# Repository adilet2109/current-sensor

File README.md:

# current-sensor
Bare-metal code base for current sensor board

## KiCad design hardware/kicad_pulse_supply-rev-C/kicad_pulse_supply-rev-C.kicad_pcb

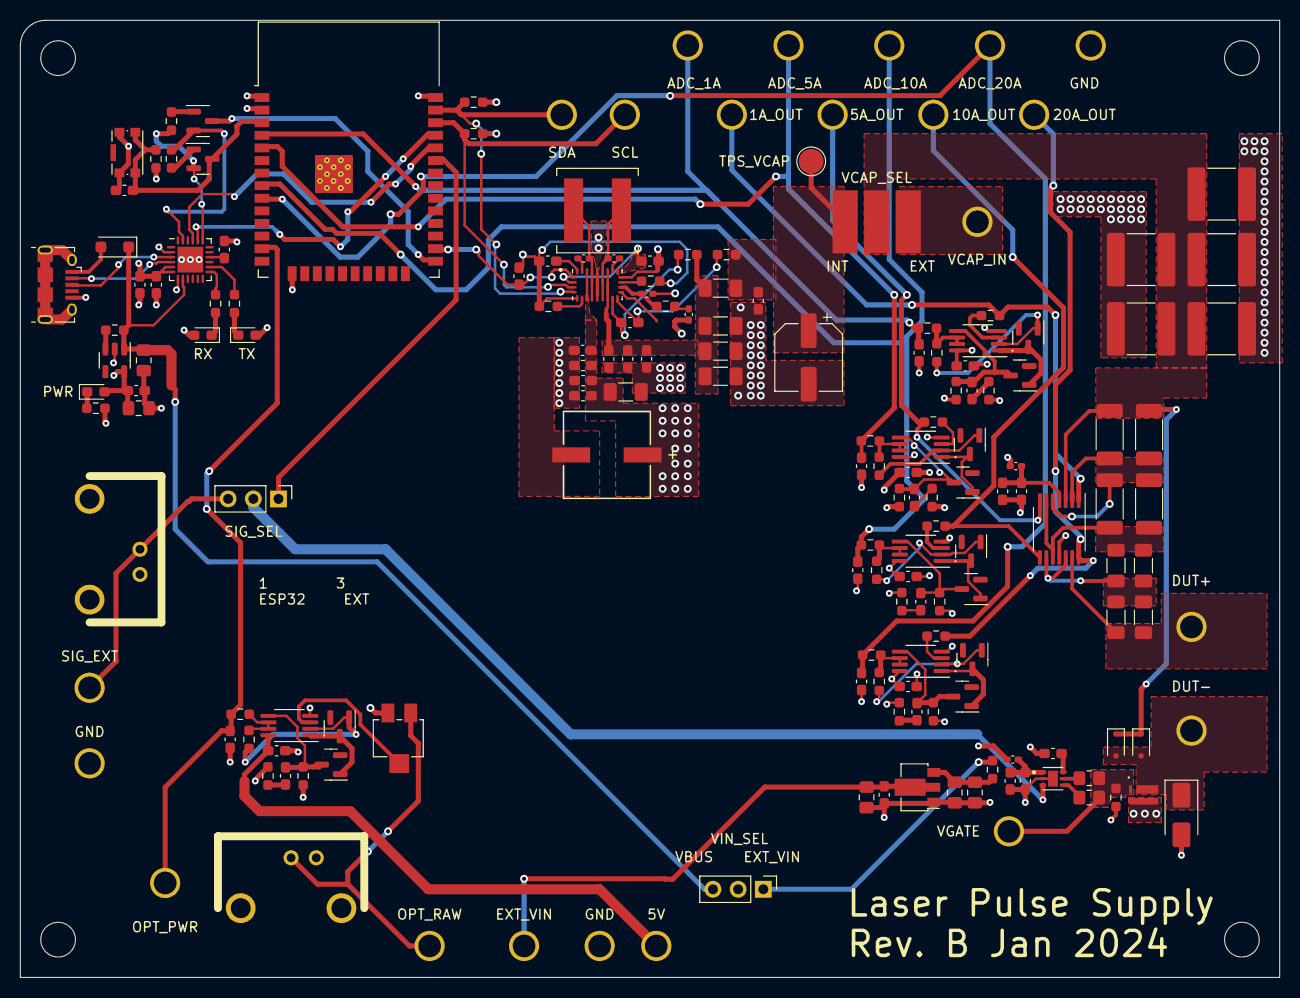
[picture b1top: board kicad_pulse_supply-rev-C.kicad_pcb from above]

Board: 4 copper layers, 127.0 x 96.5 mm, 179 parts (0 on the bottom side), 97 nets.

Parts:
C1, C3: 10u; C_0805_2012Metric_Pad1.18x1.45mm_HandSolder
C2, C4, C6, C7, C17, C18, C39, C40, C41, C42, C43, C51, C52, C59: 0u1; C_0603_1608Metric_Pad1.08x0.95mm_HandSolder
C5, C15, C16, C20, C53, C57: 1u; C_0603_1608Metric_Pad1.08x0.95mm_HandSolder
C8, C9, C10, C11, C12: 47u; C_2220_5650Metric
C14, C23, C24, C29, C32, C35: 100n; C_0603_1608Metric_Pad1.08x0.95mm_HandSolder
C19, C21, C22: 4u7; C_0805_2012Metric_Pad1.18x1.45mm_HandSolder
C25, C26, C30, C33, C36: 1u5; C_0603_1608Metric_Pad1.08x0.95mm_HandSolder
C27, C28, C31, C34, C37: 10n; C_0603_1608Metric_Pad1.08x0.95mm_HandSolder
C38: 4u7; C_0603_1608Metric_Pad1.08x0.95mm_HandSolder
C44, C54, C55, C56: 10u; C_1206_3216Metric_Pad1.33x1.80mm_HandSolder
C45: 68u; PCAP_EEHZ_F_PAN
C46, C49: 0u1; C_0402_1005Metric_Pad0.74x0.62mm_HandSolder
C47: 100p; C_0402_1005Metric_Pad0.74x0.62mm_HandSolder
C48: 4700p; C_0402_1005Metric_Pad0.74x0.62mm_HandSolder
C50: 0u22; C_0603_1608Metric_Pad1.08x0.95mm_HandSolder
C58: 100u; CP_Elec_6.3x5.8
D1: PWR; LED_0603_1608Metric_Pad1.05x0.95mm_HandSolder
D2: MBR120; D_SOD-123F
D3: TX; LED_0603_1608Metric_Pad1.05x0.95mm_HandSolder
D4: RX; LED_0603_1608Metric_Pad1.05x0.95mm_HandSolder
D5, D6: 100V 200mA; D_SOD-323F
D7: 24V 1W; D_SMA
D8, D9, D10, D11, D12, D13, D14, D15, D16, D17: BAT17; SOT-23
FB1, FB2: 330R 700mA; C_0402_1005Metric_Pad0.74x0.62mm_HandSolder
H1, H2, H3, H4: MountingHole; MountingHole_3.5mm
J1: USB_B_Micro; USB_Micro-B_Amphenol_10118194_Horizontal
J2: SIG_EXT; BNC_Molex_0731375003
J3: OPT_PWR; BNC_Molex_0731375003
JP1: SIG_SEL; PinHeader_1x03_P2.54mm_Vertical
JP2: VIN_SEL; PinHeader_1x03_P2.54mm_Vertical
JP3: VCAP_SEL; custom_jumper
L1: 4u7; L_Coilcraft_XAL7070-XXX
Q1, Q2: MMBT2222*; SOT-23
Q3: GAN7R0-150LBE; 3-FCLGA_3.2x2.2mm
R1, R2, R5, R14, R24, R25, R32, R37, R42: 10k; R_0603_1608Metric_Pad0.98x0.95mm_HandSolder
R3: 100k; R_0603_1608Metric_Pad0.98x0.95mm_HandSolder
R4, R8, R9, R26, R33, R38, R43: 1k; R_0603_1608Metric_Pad0.98x0.95mm_HandSolder
R6, R7, R22, R23, R31, R36, R41: 2k2; R_0603_1608Metric_Pad0.98x0.95mm_HandSolder
R10, R11: 0R3; R_2010_5025Metric_Pad1.40x2.65mm_HandSolder
R12, R13: 10; R_0805_2012Metric_Pad1.20x1.40mm_HandSolder
R15, R16: 0R06; R_2010_5025Metric_Pad1.40x2.65mm_HandSolder
R17, R18: 0R03; R_1206_3216Metric_Pad1.30x1.75mm_HandSolder
R19, R20: 0R015; R_1206_3216Metric_Pad1.30x1.75mm_HandSolder
R21: 0; R_0603_1608Metric_Pad0.98x0.95mm_HandSolder
R27, R28, R34, R39, R44: 1M; R_0603_1608Metric_Pad0.98x0.95mm_HandSolder
R29, R30, R35, R40, R45: 22; R_0603_1608Metric_Pad0.98x0.95mm_HandSolder
R47: 27k4; R_0603_1608Metric_Pad0.98x0.95mm_HandSolder
R48: 49k9; R_0603_1608Metric_Pad0.98x0.95mm_HandSolder
R49: 150k; R_0603_1608Metric_Pad0.98x0.95mm_HandSolder
R50, R51: 10; R_0603_1608Metric_Pad0.98x0.95mm_HandSolder
R52: 10m; R_1206_3216Metric_Pad1.30x1.75mm_HandSolder
RV1: 2k; Potentiometer_Bourns_3214X_Vertical
SW1: KMR211GLFS; SW_Push_1P1T-SH_NO_CK_KMR2xxG
TP1: SCL; Keystone-1502-2
TP2: SDA; Keystone-1502-2
TP3: VCAP_IN; Keystone-1502-2
TP4, TP10, TP16: GND; Keystone-1502-2
TP5: DUT+; Keystone-1502-2
TP6: VGATE; Keystone-1502-2
TP7: DUT-; Keystone-1502-2
TP8: 1A_OUT; Keystone-1502-2
TP9: SIG_EXT; Keystone-1502-2
TP11: 5A_OUT; Keystone-1502-2
TP12: 10A_OUT; Keystone-1502-2
TP13: 20A_OUT; Keystone-1502-2
TP14: 5V; Keystone-1502-2
TP15: EXT_VIN; Keystone-1502-2
TP17: ADC_1A; Keystone-1502-2
TP18: OPT_PEAK; Keystone-1502-2
TP19: ADC_5A; Keystone-1502-2
TP20: ADC_10A; Keystone-1502-2
TP21: ADC_20A; Keystone-1502-2
TP22: OPT_RAW; Keystone-1502-2
TP23: TPS_VCAP; TestPoint_Pad_D2.5mm
U1: AP2112K-3.3; SOT-23-5
U2: ESP32-WROOM-32D
U3: CP2104; QFN-24-1EP_4x4mm_P0.5mm_EP2.6x2.6mm
U4: MAX4378; TSSOP-14_4.4x5mm_P0.65mm
U5: UCC27611DRVT
U6: MCP1703T-5002E/MB; SOT-89-3
U7, U8, U9, U10, U11: LTC6244CMS8; MSOP-8_3x3mm_P0.65mm
U12: TPS552892RYQR; CONV_TPS552892RYQR

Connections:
+3V3: C2.1, C3.1, C5.1, C6.1, D1.2 (A), D3.2 (A), D4.2 (A), FB1.1, R2.2, R6.2, R7.2, U1.5 (VOUT), U2.2 (VDD), U3.5 (VIO), U3.6 (VDD), U3.7 (REGIN)
+5V: C23.1, C24.1, C29.1, C32.1, C35.1, C40.1, C41.1, C42.1, C43.1, C44.1, C45.1, FB2.1, JP2.2 (C), TP14.1, U7.8 (V+), U8.8 (V+), U9.8 (V+), U10.8 (V+), U11.8 (V+), U12.7 (VIN)
/Buck Boost Supply/BOOT1: C46.2, U12.20 (BOOT1)
/Buck Boost Supply/BOOT2: C49.2, U12.19 (BOOT2)
/Buck Boost Supply/COMP: C47.1, R47.1, U12.15 (COMP)
/Buck Boost Supply/ISN: C50.1, R51.1, U12.13 (ISN)
/Buck Boost Supply/ISP: C50.2, R50.1, U12.12 (ISP)
/Buck Boost Supply/SW1: C46.1, L1.1, U12.8 (SW1)
/Buck Boost Supply/SW2: C49.1, L1.2, U12.10 (SW2)
/Buck Boost Supply/Vcc: C38.1, C39.1, U12.2 (MODE), U12.18 (VCC), U12.21 (EXTVCC)
/Buck Boost Supply/Vout: C51.1, C52.1, C53.1, C54.1, C55.1, C56.1, R50.2, R52.1, U12.11 (VOUT)
/Buck Boost Supply/tps_out: C57.1, C58.1, JP3.1 (A), R51.2, R52.2, TP23.1
/ESP32/DTR: Q1.2, R5.1, U3.23 (~DTR)
/ESP32/GPIO0: Q1.3, U2.25 (IO0)
/ESP32/RESET: C4.1, Q2.3, R2.1, SW1.2, U2.3 (EN)
/ESP32/RTS: Q2.2, R1.1, U3.19 (~RTS)
/ESP32/RXD0: U2.34 (RXD0/IO3), U3.21 (TXD)
/ESP32/TXD0: U2.35 (TXD0/IO1), U3.20 (RXD)
/ESP32/d+: J1.3 (D+), U3.3 (D+)
/ESP32/d-: J1.2 (D-), U3.4 (D-)
/GaN FET and Current Sensing/OUTH: R12.1, U5.5 (OUTH)
/GaN FET and Current Sensing/OUTL: R13.1, U5.4 (OUTL)
/GaN FET and Current Sensing/in+: JP1.2 (C), U5.3 (IN+)
/GaN FET and Current Sensing/sense_out: R19.2, R20.2, TP5.1, U4.13 (-)
/GaN FET and Current Sensing/sig_ext: J2.1 (In), JP1.3 (B), TP9.1
/GaN FET and Current Sensing/vgate: Q3.1 (G), R12.2, R13.2, R14.1, TP6.1
/GaN FET and Current Sensing/vout_5v: C21.1, C22.1, R21.2, U6.3 (VO)
/GaN FET and Current Sensing/vref: C18.1, U5.6 (VREF)
ADC_1A: C25.1, R24.2, TP17.1, U2.4 (SENSOR_VP)
ADC_5A: C30.1, R32.2, TP19.1, U2.5 (SENSOR_VN)
ADC_10A: C33.1, R37.2, TP20.1, U2.8 (IO32)
ADC_20A: C36.1, R42.2, TP21.1, U2.9 (IO33)
EN/UVLO: C59.1, U2.26 (IO4), U12.1 (EN/UVLO)
GND: C1.2, C2.2, C3.2, C4.2, C5.2, C6.2, C7.2, C8.2, C9.2, C10.2, C11.2, C12.2, C14.1, C15.1, C16.2, C17.2, C18.2, C19.2, C20.2, C21.2, C22.2, C23.2, C24.2, C25.2, C26.2, C29.2, C30.2, C32.2, C33.2, C35.2, C36.2, C38.2, C39.2, C40.2, C41.2, C42.2, C43.2, C44.2, C45.2, C47.2, C48.2, C51.2, C52.2, C53.2, C54.2, C55.2, C56.2, C57.2, C58.2, C59.2, D7.2 (A), J1.5 (GND), J2.2 (Ext), J3.2 (Ext), Q3.2 (S), R4.1, R14.2, R27.2, R28.2, R29.2, R30.2, R34.2, R35.2, R39.2, R40.2, R44.2, R45.2, R48.2, R49.2, RV1.3, SW1.1, TP4.1, TP10.1, TP16.1, U1.2 (GND), U2.1 (GND), U2.15 (GND), U2.38 (GND), U2.39 (GND), U3.2 (GND), U3.25 (GND), U4.11 (GND), U5.2 (IN-), U5.7 (GND_PAD), U6.1 (GND), U7.4 (V-), U8.4 (V-), U9.4 (V-), U10.4 (V-), U11.4 (V-), U12.5 (DITH/SYNC), U12.9 (PGND), U12.17 (AGND)
unnamed: C27.2, R29.1
unnamed: C28.2, R30.1
unnamed: C31.2, R35.1
unnamed: C34.2, R40.1
unnamed: C37.2, R45.1
unnamed: C48.1, R47.2
unnamed: D1.1 (K), R4.2
unnamed: D2.2 (A), J1.1 (VBUS)
unnamed: D3.1 (K), R8.2
unnamed: D4.1 (K), R9.2
unnamed: D5.2 (A), D6.2 (A), D7.1 (K), Q3.3 (D), TP7.1
unnamed: D8.1 (A), R22.1, U7.2 (-)
unnamed: D9.1 (A), R23.1, U8.2 (-)
unnamed: D8.3 (K), D10.1 (A), U7.1
unnamed: C27.1, D10.3 (K), R27.1, U7.5 (+)
unnamed: D9.3 (K), D11.1 (A), U8.1
unnamed: C28.1, D11.3 (K), R28.1, U8.5 (+)
unnamed: D12.1 (A), R31.1, U9.2 (-)
unnamed: D12.3 (K), D13.1 (A), U9.1
unnamed: C31.1, D13.3 (K), R34.1, U9.5 (+)
unnamed: D14.1 (A), R36.1, U10.2 (-)
unnamed: D14.3 (K), D15.1 (A), U10.1
unnamed: C34.1, D15.3 (K), R39.1, U10.5 (+)
unnamed: D16.1 (A), R41.1, U11.2 (-)
unnamed: D16.3 (K), D17.1 (A), U11.1
unnamed: C37.1, D17.3 (K), R44.1, U11.5 (+)
unnamed: J3.1 (In), RV1.1, TP22.1
unnamed: JP2.1 (A), R21.1
unnamed: Q1.1, R1.2
unnamed: Q2.1, R5.2
unnamed: R3.2, U1.3 (EN)
unnamed: R9.1, U3.13 (RXT/GPIO.1)
unnamed: R8.1, U3.14 (TXT/GPIO.0)
unnamed: C7.1, U3.16 (VPP)
unnamed: R10.2, R11.2, R15.1, R16.1, U4.2 (-), U4.5 (+)
unnamed: C14.2, C15.2, FB1.2, U4.4 (VCC)
unnamed: R15.2, R16.2, R17.1, R18.1, U4.6 (-), U4.10 (+)
unnamed: R17.2, R18.2, R19.1, R20.1, U4.9 (-), U4.12 (+)
unnamed: C16.1, C17.1, FB2.2, U5.1 (VDD)
unnamed: R26.2, U7.3 (+)
unnamed: R22.2, R24.1, U7.6 (-), U7.7
unnamed: RV1.2, U8.3 (+)
unnamed: R23.2, R25.1, U8.6 (-), U8.7
unnamed: R33.2, U9.3 (+)
unnamed: R31.2, R32.1, U9.6 (-), U9.7
unnamed: R38.2, U10.3 (+)
unnamed: R36.2, R37.1, U10.6 (-), U10.7
unnamed: R43.2, U11.3 (+)
unnamed: R41.2, R42.1, U11.6 (-), U11.7
unnamed: R49.1, U12.16 (CDC)
unnamed: R48.1, U12.6 (FSW)
OPT_IN_ADC: C26.1, R25.2, TP18.1, U2.13 (IO14)
PULSE_IN: JP1.1 (A), U2.33 (IO21)
SCL: R6.1, TP1.1, U2.36 (IO22), U12.3 (PG)
SDA: R7.1, TP2.1, U2.37 (IO23), U12.4 (~CC)
SENSE_1A: R26.1, TP8.1, U4.1
SENSE_5A: R33.1, TP11.1, U4.7
SENSE_10A: R38.1, TP12.1, U4.8
SENSE_20A: R43.1, TP13.1, U4.14
VBUS: C1.1, D2.1 (K), JP2.3 (B), R3.1, U1.1 (VIN), U3.8 (VBUS)
VCAP: C8.1, C9.1, C10.1, C11.1, C12.1, D5.1 (K), D6.1 (K), JP3.2 (C), R10.1, R11.1, U4.3 (+)
VCAP_EXT: JP3.3 (B), TP3.1
VIN: C19.1, C20.1, TP15.1, U6.2 (VI)

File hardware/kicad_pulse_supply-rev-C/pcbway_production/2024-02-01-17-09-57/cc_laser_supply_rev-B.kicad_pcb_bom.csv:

designator,quantity,value,pack,mpn,mount_type
"C1, C3",2,10u,C_0805_2012Metric_Pad1.18x1.45mm_HandSolder,,smt
"C10, C11, C12, C8, C9",5,47u,C_2220_5650Metric,C5750X7R1V476M230KC,smt
C13,1,22m,CP_Radial_D35.0mm_P10.00mm_SnapIn,,tht
"C14, C23, C24, C29, C32, C35",6,100n,C_0603_1608Metric_Pad1.08x0.95mm_HandSolder,,smt
"C15, C16, C20, C5, C53, C57",6,1u,C_0603_1608Metric_Pad1.08x0.95mm_HandSolder,,smt
"C17, C18, C2, C39, C4, C40, C41, C42, C43, C51, C52, C59, C6, C7",14,0u1,C_0603_1608Metric_Pad1.08x0.95mm_HandSolder,,smt
"C19, C21, C22",3,4u7,C_0805_2012Metric_Pad1.18x1.45mm_HandSolder,,smt
"C25, C26, C30, C33, C36",5,1u5,C_0603_1608Metric_Pad1.08x0.95mm_HandSolder,,smt
"C27, C28, C31, C34, C37",5,10n,C_0603_1608Metric_Pad1.08x0.95mm_HandSolder,,smt
C38,1,4u7,C_0603_1608Metric_Pad1.08x0.95mm_HandSolder,,smt
"C44, C54, C55, C56",4,10u,C_1206_3216Metric_Pad1.33x1.80mm_HandSolder,,smt
C45,1,68u,PCAP_EEHZ_F_PAN,EEH-ZA1H680P,smt
"C46, C49",2,0u1,C_0402_1005Metric_Pad0.74x0.62mm_HandSolder,,smt
C47,1,100p,C_0402_1005Metric_Pad0.74x0.62mm_HandSolder,CGA2B2C0G1H101J,smt
C48,1,4700p,C_0402_1005Metric_Pad0.74x0.62mm_HandSolder,CGA2B2X7R1H472K,smt
C50,1,0u22,C_0603_1608Metric_Pad1.08x0.95mm_HandSolder,,smt
C58,1,100u,CP_Elec_6.3x5.8,EEHZK1V101XP ,smt
D1,1,PWR,LED_0603_1608Metric_Pad1.05x0.95mm_HandSolder,,smt
"D10, D11, D12, D13, D14, D15, D16, D17, D8, D9",10,BAT17,SOT-23,,smt
D2,1,MBR120,D_SOD-123F,,smt
D3,1,TX,LED_0603_1608Metric_Pad1.05x0.95mm_HandSolder,,smt
D4,1,RX,LED_0603_1608Metric_Pad1.05x0.95mm_HandSolder,,smt
"D5, D6",2,100V 200mA,D_SOD-323F,,smt
D7,1,24V 1W,D_SMA,,smt
"FB1, FB2",2,330R 700mA,C_0402_1005Metric_Pad0.74x0.62mm_HandSolder,,smt
"H1, H2, H3, H4",4,MountingHole,MountingHole_3.5mm,,tht
J1,1,USB_B_Micro,USB_Micro-B_Amphenol_10118194_Horizontal,,smt
J2,1,SIG_EXT,BNC_Molex_0731375003,,tht
J3,1,OPT_PWR,BNC_Molex_0731375003,,tht
JP1,1,SIG_SEL,PinHeader_1x03_P2.54mm_Vertical,,tht
JP2,1,VIN_SEL,PinHeader_1x03_P2.54mm_Vertical,,tht
JP3,1,VCAP_SEL,custom_jumper,,smt
L1,1,4u7,L_Coilcraft_XAL7070-XXX,XAL7070-472MEC,smt
"Q1, Q2",2,MMBT2222*,SOT-23,,smt
Q3,1,GAN7R0-150LBE,3-FCLGA_3.2x2.2mm,,smt
"R1, R14, R2, R24, R25, R32, R37, R42, R5",9,10k,R_0603_1608Metric_Pad0.98x0.95mm_HandSolder,,smt
"R10, R11",2,0R3,R_2010_5025Metric_Pad1.40x2.65mm_HandSolder,,smt
"R12, R13",2,10,R_0805_2012Metric_Pad1.20x1.40mm_HandSolder,,smt
"R15, R16",2,0R06,R_2010_5025Metric_Pad1.40x2.65mm_HandSolder,,smt
"R17, R18",2,0R03,R_1206_3216Metric_Pad1.30x1.75mm_HandSolder,,smt
"R19, R20",2,0R015,R_1206_3216Metric_Pad1.30x1.75mm_HandSolder,,smt
R21,1,0,R_0603_1608Metric_Pad0.98x0.95mm_HandSolder,,smt
"R22, R23, R31, R36, R41, R6, R7",7,2k2,R_0603_1608Metric_Pad0.98x0.95mm_HandSolder,,smt
"R26, R33, R38, R4, R43, R8, R9",7,1k,R_0603_1608Metric_Pad0.98x0.95mm_HandSolder,,smt
"R27, R28, R34, R39, R44",5,1M,R_0603_1608Metric_Pad0.98x0.95mm_HandSolder,,smt
"R29, R30, R35, R40, R45",5,22,R_0603_1608Metric_Pad0.98x0.95mm_HandSolder,,smt
R3,1,100k,R_0603_1608Metric_Pad0.98x0.95mm_HandSolder,,smt
R46,1,102k,R_0603_1608Metric_Pad0.98x0.95mm_HandSolder,,smt
R47,1,27k4,R_0603_1608Metric_Pad0.98x0.95mm_HandSolder,,smt
R48,1,49k9,R_0603_1608Metric_Pad0.98x0.95mm_HandSolder,,smt
R49,1,150k,R_0603_1608Metric_Pad0.98x0.95mm_HandSolder,,smt
"R50, R51",2,10,R_0603_1608Metric_Pad0.98x0.95mm_HandSolder,,smt
R52,1,10m,R_1206_3216Metric_Pad1.30x1.75mm_HandSolder,CRF1206-FZ-R010ELF,smt
RV1,1,2k,Potentiometer_Bourns_3214X_Vertical,3214X-1-202E,smt
SW1,1,KMR211GLFS,SW_Push_1P1T-SH_NO_CK_KMR2xxG,,smt
TP1,1,SCL,Keystone-1502-2,,tht
"TP10, TP16, TP4",3,GND,Keystone-1502-2,,tht
TP11,1,5A_OUT,Keystone-1502-2,,tht
TP12,1,10A_OUT,Keystone-1502-2,,tht
TP13,1,20A_OUT,Keystone-1502-2,,tht
TP14,1,5V,Keystone-1502-2,,tht
TP15,1,EXT_VIN,Keystone-1502-2,,tht
TP17,1,ADC_1A,Keystone-1502-2,,tht
TP18,1,OPT_PEAK,Keystone-1502-2,,tht
TP19,1,ADC_5A,Keystone-1502-2,,tht
TP2,1,SDA,Keystone-1502-2,,tht
TP20,1,ADC_10A,Keystone-1502-2,,tht
TP21,1,ADC_20A,Keystone-1502-2,,tht
TP22,1,OPT_RAW,Keystone-1502-2,,tht
TP23,1,TPS_VCAP,TestPoint_Pad_D2.5mm,,tht
TP3,1,VCAP_IN,Keystone-1502-2,,tht
TP5,1,DUT+,Keystone-1502-2,,tht
TP6,1,VGATE,Keystone-1502-2,,tht
TP7,1,DUT-,Keystone-1502-2,,tht
TP8,1,1A_OUT,Keystone-1502-2,,tht
TP9,1,SIG_EXT,Keystone-1502-2,,tht
U1,1,AP2112K-3.3,SOT-23-5,,smt
"U10, U11, U7, U8, U9",5,LTC6244CMS8,MSOP-8_3x3mm_P0.65mm,,smt
U12,1,TPS552892RYQR,CONV_TPS552892RYQR,,smt
U2,1,ESP32-WROOM-32D,ESP32-WROOM-32D,,smt
U3,1,CP2104,QFN-24-1EP_4x4mm_P0.5mm_EP2.6x2.6mm,,smt
U4,1,MAX4378,TSSOP-14_4.4x5mm_P0.65mm,,smt
U5,1,UCC27611DRVT,UCC27611DRVT,,smt
U6,1,MCP1703T-5002E/MB,SOT-89-3,,smt

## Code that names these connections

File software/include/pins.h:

/*
    Filename:       pins.h
    Date:           08-Mar-2024
    Description:    Pin definitions for the ESP32-WROOM module
*/

#ifndef PINS_H
#define PINS_H

#define PIN_PULSE_OUTPUT 21
#define PIN_ADC_1A 36
#define PIN_ADC_5A 39
#define PIN_ADC_10A 32
#define PIN_ADC_20A 33
#define PIN_ADC_OPT 14
#define ENABLE_PIN 34
#define DECREASE_PIN 25
#define INCREASE_PIN 26
#define TIMER_PIN 32
#define TPS55289_EN_PIN 4

#endif

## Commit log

2024-02-08 code added
2024-02-08 added kicad file
2024-02-08 made seperate directory for software files
2024-03-08 Project set up in PlatformIO
    Working base project in PlatformIO which incorporates Dave's CurrentSensorBoard3.ino into my existing ESP32 ADC project. No functionality changes, just a base to start with main branch.
2024-03-08 Setting up .gitignore in software folder
2024-03-08 finished incorporating .ino file and reformatted code
2024-03-08 Created pulser library
2024-03-13 Drafted README.md
2024-04-02 Board bringup: added TPS commands
2024-04-09 Adjusted software .gitignore
2024-04-09 Started TODO for hardware rev C
2024-04-09 Formatted code (no changes)
2024-04-09 Tracking .gitignore
2024-04-09 Fixed issue with min vout stuck at 1.6V
2024-04-09 Working on TPS55289 boost issues
2024-04-12 Adding PCB issues to be fixed in rev C
2024-04-16 updated .gitignore
2024-04-16 Stopped tracking and removed kicad*.zip files from index
2024-04-16 Further update to .gitignore
2024-04-16 More .gitignore stuff
2024-04-16 Fixed conflicting .gitignores
